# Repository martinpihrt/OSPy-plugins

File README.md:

# OSPy-plugins

### A collection of user contributed plugins for the Raspberry Pi based irrigation controll software OSPy - Open Sprinkler Python (OSPy).

Please note: Unless otherwise stated: This is free software: you can redistribute it and/or modify it under the terms of the GNU General Public License as published by the Free Software Foundation, either version 3 of the License, or (at your option) any later version.

## Documentation

The complete [OSPy-plugins Wiki](https://github.com/martinpihrt/OSPy-plugins/wiki) explains what every official plug-in is for, how it works, how to install and configure it, its dependencies, hardware, permissions and troubleshooting steps. Start with [Getting started](https://github.com/martinpihrt/OSPy-plugins/wiki/Getting-Started) or browse the [plug-in catalog](https://github.com/martinpihrt/OSPy-plugins/wiki/Plugin-Catalog).

## Stable and test channels

The `master` branch is the stable channel selected by OSPy by default. New plug-in changes are developed and verified in the `beta` branch first. After successful practical and automated testing, the same commits can be promoted from `beta` to `master` without rebuilding or changing them.

GitHub Actions runs the OSPy test suite on every push and pull request to `beta` or `master`. The tested plug-in revision is checked against both the OSPy `master` and OSPy `beta` branches on Python 3.11 and Python 3.14. All four jobs must pass before a beta change is promoted to the stable channel. Python 3.11 remains the Raspberry Pi OS Bookworm baseline and Python 3.14 verifies compatibility with the latest stable Python feature release.

## Declared permission approval

Every `plugin.json` must declare only the permissions the plug-in actually uses: `network`, `files`, `i2c`, `gpio`, `email`, `subprocess` and/or `system`. Starting with OSPy 3.0.294, newly installed plug-ins require explicit administrator approval of that complete set before their Python code starts. An update with the same or fewer permissions keeps its approval. Adding a permission requires a new approval and is skipped by automatic update until it has been reviewed. Existing installed plug-ins are approved once during the backward-compatible OSPy upgrade migration, including disabled plug-ins.

This is administrative consent and an audit record, not operating-system sandboxing. Plug-in authors must increase the manifest version whenever code or declared requirements change and must never omit a permission merely to avoid the approval prompt.

These programs are distributed in the hope that they will be useful, but WITHOUT ANY WARRANTY; without even the implied warranty of MERCHANTABILITY or FITNESS FOR A PARTICULAR PURPOSE. See the GNU General Public License for more details. http://opensource.org/licenses/gpl-3.0.html

Theses I2C addresses is used in available plugins:
* air_temp_humi	0x03<br>
* tank_monitor 	0x04<br>
* button_contr	0x27<br>
* lcd_display 	0x20-0x27, 0x38-0x3F<br>
* real_time 	0x68<br>
* volt_temp_da 	0x48<br>
* water_meter 	one selectable address: 0x50 or 0x51<br>
* wind_monitor 	one selectable address: 0x50 or 0x51<br>
* current_loop_tanks_monitor 0x48, 0x49, 0x4A, 0x4B<br>

Address conflicts, selectable alternatives and wiring requirements are documented in [Hardware and I²C](https://github.com/martinpihrt/OSPy-plugins/wiki/Hardware-and-I2C) and on the individual plug-in pages.

## Available plug-ins

This table is generated from the `name`, `version` and `description` fields in every official `plugin.json`. Run `python tools/generate_plugin_table.py` after changing a manifest and `python tools/generate_plugin_table.py --check` to verify that the README is current.

<!-- plugin-table:start -->
| Plug-in | Version | Description |
| --- | --- | --- |
| [**Air Temperature and Humidity Monitor**](https://github.com/martinpihrt/OSPy-plugins/wiki/Plugin-air-temp-humi) | `1.0.7` | Monitors DHT temperature and humidity and optional DS18B20 sensors through an external I2C board. |
| [**Astro Sunrise and Sunset**](https://github.com/martinpihrt/OSPy-plugins/wiki/Plugin-sunrise-and-sunset) | `1.0.6` | Calculates astronomical dawn, sunrise, noon, sunset and dusk times for OSPy programs and mobile clients. |
| [**Automation Rules**](https://github.com/martinpihrt/OSPy-plugins/wiki/Plugin-automation-rules) | `1.1.4` | Builds graphical AND/OR rules over cached provider and OSPy values, sends detailed notifications and optionally performs guarded control actions with incident locking. |
| [**Button Control**](https://github.com/martinpihrt/OSPy-plugins/wiki/Plugin-button-control) | `1.0.0` | Controls OSPy functions through eight MCP23017 I2C buttons and indicator LEDs. |
| [**CHMI**](https://github.com/martinpihrt/OSPy-plugins/wiki/Plugin-chmi) | `1.0.7` | Downloads CHMI or SHMU radar data, detects local rain and optionally controls a hardware map. |
| [**CLI Control**](https://github.com/martinpihrt/OSPy-plugins/wiki/Plugin-cli-control) | `1.0.0` | Runs administrator-configured shell commands when OSPy station states change. |
| [**Current Loop Tanks Monitor**](https://github.com/martinpihrt/OSPy-plugins/wiki/Plugin-current-loop-tanks-monitor) | `1.1.1` | Monitors up to four water tanks through an ADS1115 and 4-20 mA pressure sensors. |
| [**Database Connector**](https://github.com/martinpihrt/OSPy-plugins/wiki/Plugin-database-connector) | `1.1.3` | Provides shared MySQL access, backup and durable queued writes for OSPy plug-ins. |
| [**Direct 16 Relay Outputs**](https://github.com/martinpihrt/OSPy-plugins/wiki/Plugin-relay-16) | `1.0.0` | Controls up to 16 direct Raspberry Pi GPIO relay outputs with configurable trigger polarity. |
| [**Door Opening**](https://github.com/martinpihrt/OSPy-plugins/wiki/Plugin-door-opening) | `1.0.0` | Activates a selected OSPy station for a bounded door or gate opening interval. |
| [**E-mail Notifications**](https://github.com/martinpihrt/OSPy-plugins/wiki/Plugin-email-notifications) | `1.0.1` | Sends OSPy event notifications through a STARTTLS SMTP server with an optional retry queue. |
| [**E-mail Notifications SSL**](https://github.com/martinpihrt/OSPy-plugins/wiki/Plugin-email-notifications-ssl) | `1.1.6` | Sends OSPy event and login notifications through SMTP over SSL with an optional retry queue. |
| [**E-mail Reader**](https://github.com/martinpihrt/OSPy-plugins/wiki/Plugin-email-reader) | `1.0.0` | Reads authenticated IMAP commands and controls OSPy programs, stations and system functions. |
| [**Energy Meter**](https://github.com/martinpihrt/OSPy-plugins/wiki/Plugin-energy-meter) | `1.0.7` | Monitors Shelly three-phase electricity meters and stores import, export, tariff, cost and solar calculations. |
| [**Home Assistant**](https://github.com/martinpihrt/OSPy-plugins/wiki/Plugin-mqtt-home-assistant) | `1.0.1` | Publishes OSPy devices, controls and sensor values through Home Assistant MQTT Discovery. |
| [**IP Cam**](https://github.com/martinpihrt/OSPy-plugins/wiki/Plugin-ip-cam) | `1.0.0` | Downloads, caches and proxies JPEG, GIF and MJPEG images from IP cameras. |
| [**IP Scanner**](https://github.com/martinpihrt/OSPy-plugins/wiki/Plugin-ip-scanner) | `1.0.0` | Scans the local network for devices, names, MAC addresses and common web services. |
| [**Irrigation Safety**](https://github.com/martinpihrt/OSPy-plugins/wiki/Plugin-irrigation-safety) | `1.0.0` | Monitors irrigation flow, pressure and tank level, learns station flow ranges and can stop outputs and disable the scheduler when a confirmed fault occurs. |
| [**Label Maker**](https://github.com/martinpihrt/OSPy-plugins/wiki/Plugin-labelmaker) | `1.0.0` | Generates EAN13 barcodes and configurable QR code images. |
| [**LCD Display**](https://github.com/martinpihrt/OSPy-plugins/wiki/Plugin-lcd-display) | `1.0.2` | Displays OSPy status information on a 16x2 HD44780 LCD through a PCF8574 I2C expander. |
| [**Modbus Stations**](https://github.com/martinpihrt/OSPy-plugins/wiki/Plugin-modbus-stations) | `1.0.0` | Controls OSPy station outputs through Modbus RTU serial relay boards. |
| [**Monthly Water Level**](https://github.com/martinpihrt/OSPy-plugins/wiki/Plugin-monthly-water-level) | `1.0.1` | Applies a configurable irrigation percentage adjustment for each calendar month. |
| [**MQTT**](https://github.com/martinpihrt/OSPy-plugins/wiki/Plugin-mqtt) | `1.0.1` | Shared MQTT client, status publishing and remote OSPy control. |
| [**Network Ping Monitor**](https://github.com/martinpihrt/OSPy-plugins/wiki/Plugin-network-ping-monitor) | `1.0.2` | Monitors three network targets through ICMP and optionally logs availability and latency. |
| [**OSPy package Backup**](https://github.com/martinpihrt/OSPy-plugins/wiki/Plugin-ospy-backup) | `1.0.5` | Creates downloadable ZIP archives of installed plug-in data directories. |
| [**Photovoltaic Boiler**](https://github.com/martinpihrt/OSPy-plugins/wiki/Plugin-photovoltaic-boiler) | `1.0.0` | Controls boiler heating between photovoltaic surplus and the public grid using configured temperature sources. |
| [**Ping Monitor**](https://github.com/martinpihrt/OSPy-plugins/wiki/Plugin-ping-monitor) | `1.0.0` | Monitors host reachability, logs outages and can notify or restart a device after repeated failures. |
| [**Pool Heating**](https://github.com/martinpihrt/OSPy-plugins/wiki/Plugin-pool-heating) | `1.0.0` | Controls a pool circulation pump from pool and solar collector temperatures. |
| [**Pressure Monitor**](https://github.com/martinpihrt/OSPy-plugins/wiki/Plugin-pressure-monitor) | `1.1.1` | Checks binary pipe pressure while the master station runs and can stop irrigation when pressure is missing. |
| [**Pressurizer**](https://github.com/martinpihrt/OSPy-plugins/wiki/Plugin-pressurizer) | `1.0.0` | Pre-runs the master pump to build pressure before selected irrigation stations start. |
| [**Proto**](https://github.com/martinpihrt/OSPy-plugins/wiki/Plugin-proto) | `1.0.0` | Provides a minimal working example and starting point for developing OSPy plug-ins. |
| [**Pulse Output Test**](https://github.com/martinpihrt/OSPy-plugins/wiki/Plugin-pulse) | `1.0.0` | Pulses a selected OSPy station at 1 Hz for a bounded valve-location test. |
| [**Real Time and NTP time**](https://github.com/martinpihrt/OSPy-plugins/wiki/Plugin-real-time) | `1.0.1` | Synchronizes system time with NTP and supported I2C real-time clocks. |
| [**Relay Test**](https://github.com/martinpihrt/OSPy-plugins/wiki/Plugin-relay) | `1.0.0` | Runs a bounded test of the OSPy relay output. |
| [**Remote FTP Control**](https://github.com/martinpihrt/OSPy-plugins/wiki/Plugin-remote-ftp-control) | `1.0.0` | Exchanges command and status files through FTP for legacy remote control of OSPy. |
| [**Remote Notifications**](https://github.com/martinpihrt/OSPy-plugins/wiki/Plugin-remote-notifications) | `1.0.0` | Sends OSPy status and event notifications to a configured remote PHP and SQL web service. |
| [**RS485 Communication**](https://github.com/martinpihrt/OSPy-plugins/wiki/Plugin-rs485-communication) | `1.0.3` | Provides a central RS485 worker and FIFO rs485_queue for OSPy plug-ins, with Waveshare CH343G auto-detection, status monitoring and adapter testing. |
| [**Shelly Cloud Integration**](https://github.com/martinpihrt/OSPy-plugins/wiki/Plugin-shelly-cloud-integrator) | `1.0.8` | Loads and caches configured Shelly device states from the Shelly Cloud API for OSPy and other plug-ins. |
| [**Signaling Examples**](https://github.com/martinpihrt/OSPy-plugins/wiki/Plugin-signaling-examples) | `1.0.0` | Demonstrates OSPy and plug-in signal subscriptions and records received events. |
| [**SMS Modem**](https://github.com/martinpihrt/OSPy-plugins/wiki/Plugin-sms-adj) | `1.0.0` | Receives authorized SMS commands through a Gammu-compatible modem and returns OSPy status by SMS. |
| [**Speed Monitor**](https://github.com/martinpihrt/OSPy-plugins/wiki/Plugin-speed-monitor) | `1.0.0` | Measures and logs Internet ping, download and upload performance at scheduled intervals. |
| [**System Debug Information**](https://github.com/martinpihrt/OSPy-plugins/wiki/Plugin-system-debug) | `1.0.1` | Displays, downloads and clears the OSPy technical debug log. |
| [**System Information**](https://github.com/martinpihrt/OSPy-plugins/wiki/Plugin-system-info) | `1.0.1` | Displays operating-system, hardware, network, process, storage, USB, serial and optional I2C information. |
| [**System Update**](https://github.com/martinpihrt/OSPy-plugins/wiki/Plugin-system-update) | `1.2.8` | Checks, installs and safely rolls back OSPy updates from stable or beta Git branches with backup and watchdog protection. |
| [**System Watchdog**](https://github.com/martinpihrt/OSPy-plugins/wiki/Plugin-system-watchdog) | `1.0.0` | Configures and monitors the Raspberry Pi hardware watchdog to recover from system lockups. |
| [**Telegram Bot**](https://github.com/martinpihrt/OSPy-plugins/wiki/Plugin-telegram-bot) | `1.0.1` | Sends Telegram notifications and accepts a limited set of OSPy control commands from subscribed chats. |
| [**Temperature Switch**](https://github.com/martinpihrt/OSPy-plugins/wiki/Plugin-temperature-switch) | `1.0.0` | Starts and stops OSPy programs from configured temperature sources and hysteresis limits. |
| [**Thermostat**](https://github.com/martinpihrt/OSPy-plugins/wiki/Plugin-thermostat) | `1.1.4` | Controls up to 20 OSPy programs from temperature sources, hysteresis limits, operating windows and a heating-water condition. |
| [**UPS Monitor**](https://github.com/martinpihrt/OSPy-plugins/wiki/Plugin-ups-adj) | `1.0.5` | Monitors mains power and can notify, shut down OSPy and switch off a UPS after a sustained outage. |
| [**Usage Statistics**](https://github.com/martinpihrt/OSPy-plugins/wiki/Plugin-usage-statistics) | `1.0.1` | Downloads and displays anonymized public OSPy usage statistics. |
| [**Venetian Blind**](https://github.com/martinpihrt/OSPy-plugins/wiki/Plugin-venetian-blind) | `1.2.8` | Controls configured Shelly or compatible blinds, including tilt positions, automation rules and mobile actions. |
| [**Voice Notification**](https://github.com/martinpihrt/OSPy-plugins/wiki/Plugin-voice-notification) | `1.0.0` | Plays scheduled voice announcements before configured OSPy program and station events. |
| [**Voice Station**](https://github.com/martinpihrt/OSPy-plugins/wiki/Plugin-voice-station) | `1.0.0` | Queues and plays audio when station outputs change, regardless of what triggered the station. |
| [**Voltage and Temperature Monitor**](https://github.com/martinpihrt/OSPy-plugins/wiki/Plugin-volt-temp-da) | `1.0.0` | Measures and logs voltages or LM35 temperatures through a PCF8591 I2C converter. |
| [**Water Consumption Counter**](https://github.com/martinpihrt/OSPy-plugins/wiki/Plugin-water-consumption-counter) | `1.2.7` | Estimates and reports water consumption from configured station flow rates and master-station runtime. |
| [**Water Meter**](https://github.com/martinpihrt/OSPy-plugins/wiki/Plugin-water-meter) | `1.2.1` | Measures pulse-output water meters through a PCF8583 counter with live flow, history, CSV and optional SQL logging. |
| [**Water Tank Monitor**](https://github.com/martinpihrt/OSPy-plugins/wiki/Plugin-tank-monitor) | `1.1.1` | Measures ultrasonic tank level and volume, blocks irrigation on low water and exposes tank provider actions. |
| [**Weather Dashboard**](https://github.com/martinpihrt/OSPy-plugins/wiki/Plugin-weather-dashboard) | `1.0.2` | Displays selected OSPy sensor and plug-in values as configurable gauges or text. |
| [**Weather Stations**](https://github.com/martinpihrt/OSPy-plugins/wiki/Plugin-weather-stations) | `1.0.0` | Displays selected OSPy sensor and plug-in values as configurable gauges or text. |
| [**Weather-based Rain Delay**](https://github.com/martinpihrt/OSPy-plugins/wiki/Plugin-weather-based-rain-delay) | `1.0.0` | Sets OSPy rain delay from measured or Netatmo rainfall and configured weather thresholds. |
| [**Weather-based Water Level**](https://github.com/martinpihrt/OSPy-plugins/wiki/Plugin-weather-based-water-level) | `1.1.2` | Calculates hourly OSPy water-level adjustment from weather balance, Zimmerman or evapotranspiration methods. |
| [**Weather-based Water Level Netatmo**](https://github.com/martinpihrt/OSPy-plugins/wiki/Plugin-weather-based-water-level-netatmo) | `1.0.0` | Adjusts OSPy water level using rainfall history from a configured Netatmo rain module. |
| [**Webcam Monitor**](https://github.com/martinpihrt/OSPy-plugins/wiki/Plugin-webcam) | `1.0.0` | Captures and serves snapshots from a Linux USB webcam using fswebcam. |
| [**Wind Speed Monitor**](https://github.com/martinpihrt/OSPy-plugins/wiki/Plugin-wind-monitor) | `1.2.3` | Measures wind through PCF8583 or Modbus sensors and can log, notify or run safety actions. |
<!-- plugin-table:end -->

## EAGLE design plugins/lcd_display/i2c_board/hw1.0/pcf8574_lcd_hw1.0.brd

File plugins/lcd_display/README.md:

LCD Settings Readme
====

Version 1.0.1 disconnects all OSPy signal receivers when the plug-in worker
stops, preventing stale callbacks after a plug-in restart.

Tested in Python 3+

This plugin shows information on 16x2 character LCD with PCF8574.  
Automatically detects the display at the following I2C addresses: 0x20-0x27, 0x38-0x3F.  
Compatible with the HD44780 controller.  

The plug-in includes an OSPy `plugin.json` manifest, uses the shared plug-in runtime and implements `health()`. Diagnostics reports whether the display function and worker are running, the detected I2C address, the last successful LCD update and the most recent I2C error. A temporarily busy shared I2C bus is reported as a warning; a persistent write error is reported as an error.

Plugin setup
-----------
* Check Use I2C LCD:  
  If checked use I2C lcd plugin is enabled and print messages on the LCD display.  </br>

* HW version I2C PCF8574<->LCD:  
  Select type Hardware board with PCF8574. Conection with LCD driver:  
  a) Lower 4 bits of expander are commands bits  
  b) Top 4 bits of expander are commands bits AND P0-4 P1-5 P2-6 (Use for LCD1602 board)  
  c) Top 4 bits of expander are commands bits AND P0-6 P1-5 P2-4  
  d) LCD1602 board where lower 4 are commands, but backlight is pin 3  
  e) LCD board (https://pihrt.com/clanky/arduino-uno-deska-i2c-lcd-16x2)  </br>

* Check Use print lines to debug files:  
  If checked use print lines to debug files line 1 or line 2 print to debug files.  
  (warning: If you enable this debug file will have a huge size).  </br>

* Display: If checked print state message to LCD display
System Name:  
SW Version Date:  
IP:  
Port:  
CPU Temp:  
Time and Date:
Uptime:  
Rain Sensor:  
Last Run Program:  
Pressure Sensor:  
Water Tank Level:  
Running Stations:  
DS18B20 Temperature: </br>
Wind Speed:
Shows current wind speed and maximum wind speed from the Wind Speed Monitor plugin in the format `actual (max) unit`. </br>

The LCD controller is re-initialized at the start of each display cycle without re-scanning the I2C address. This helps recover HD44780/PCF8574 displays that drift into corrupted characters during long running operation. </br>

* Status:
  Status window from the plugin.  
  Example message on the LCD display:  
  OpenSprinkler Py (text on line 1)
  Irrigation system (text on line 2)    
  CPU temperature:  
  42.8 C  
  Date: 17.02.2015  
  Time: 12:22:57  
  OSPy version:  
  2015-02-17  
  System uptime:  
  5:12:11  
  My IP is:  
  https://192.168.4.184/8080  
  My port is:  
  8080  
  Rain sensor:  
  Inactive  
  Last program:  
  None  
  Pressure sensor:    
  Not available  
  Water Tank Level:
  Level 120 cm 100%, volume 1.25 m3, ping 86 cm
  DS1-6 Temperature:  
  23.5, -127, 23.5, 36.5, 78.0, -127
  (-127 is not connected probe to hardware board...)  </br>

* Important status information OSPy:
  If events occur in the system: restart, poweroff, update available, they will be displayed preferentially regardless of the above settings.  </br>     
  
## The hardware should be connected as follows (LCD board by pihrt.com)

## The LCD 1602 IIC with PCF8574 (Top 4 bits of expander are commands bits AND P0-4 P1-5 P2-6)

## PCF8574 address map

Visit [Martin Pihrt's blog](https://pihrt.com/clanky/arduino-uno-deska-i2c-lcd-16x2). for more information.

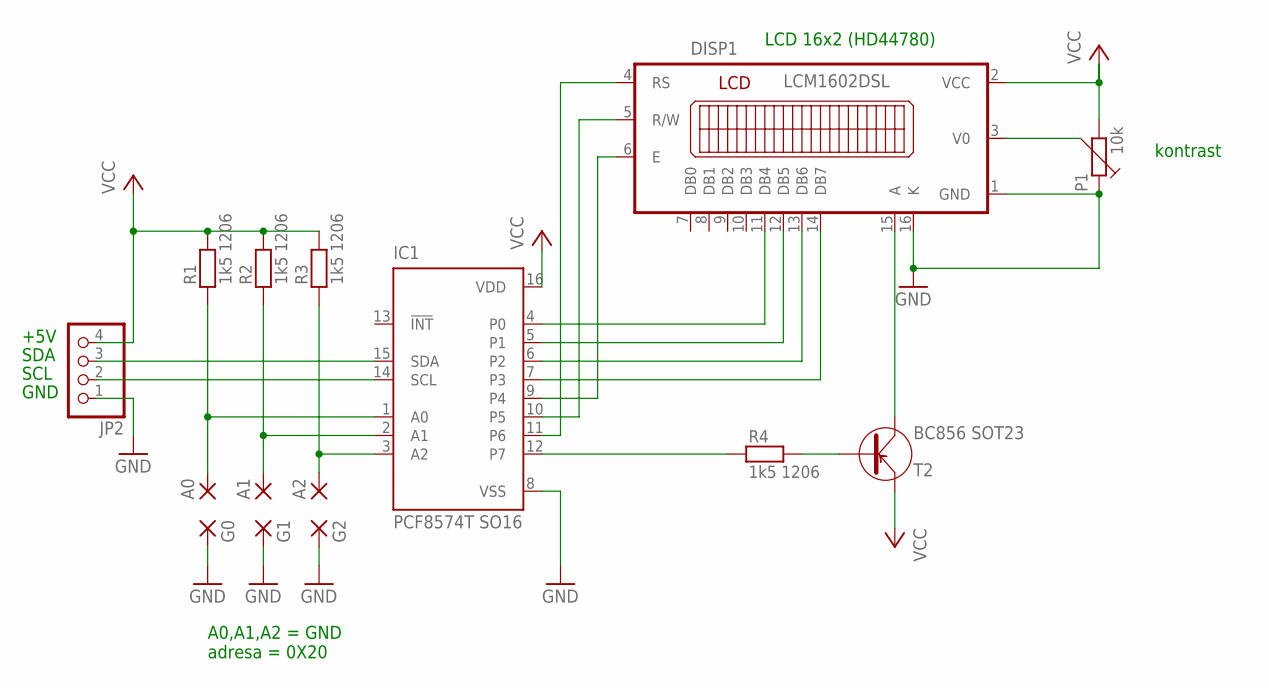
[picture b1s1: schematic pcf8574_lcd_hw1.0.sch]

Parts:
A0, A1, A2: SMD2; SMD1,27-2,54
DISP1: LCM1602DSL
G0, G1, G2: SMD2; SMD1,27-2,54
IC1: PCF8574T SO16; SO16W
JP2: PINHD-1X4; 1X04
P1: 10k; PT10V
R1, R2, R3, R4: 1k5 1206; 1206
T2: BC856 SOT23; SOT-23

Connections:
GND: DISP1.1 (GND), DISP1.16 (K), G0.1, G1.1, G2.1, IC1.8 (VSS), JP2.1, P1.1
unnamed: IC1.15 (SDA), JP2.3
unnamed: IC1.14 (SCL), JP2.2
unnamed: DISP1.3 (V0), P1.3
unnamed: DISP1.15 (A), T2.3 (C)
unnamed: DISP1.4 (RS), IC1.11 (P6)
unnamed: DISP1.5 (R/W), IC1.10 (P5)
unnamed: DISP1.6 (E), IC1.9 (P4)
unnamed: DISP1.14 (DB7), IC1.7 (P3)
unnamed: IC1.12 (P7), R4.1
unnamed: A0.1, IC1.1 (A0), R1.1
unnamed: A2.1, IC1.3 (A2), R3.1
unnamed: A1.1, IC1.2 (A1), R2.1
unnamed: DISP1.13 (DB6), IC1.6 (P2)
unnamed: DISP1.12 (DB5), IC1.5 (P1)
unnamed: DISP1.11 (DB4), IC1.4 (P0)
unnamed: R4.2, T2.1 (B)
VCC: DISP1.2 (VCC), IC1.16 (VDD), JP2.4, P1.2, R1.2, R2.2, R3.2, T2.2 (E)

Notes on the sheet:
+5V
SDA
SCL
GND
kontrast
A0,A1,A2 = GND adresa = 0X20
LCD 16x2 (HD44780)

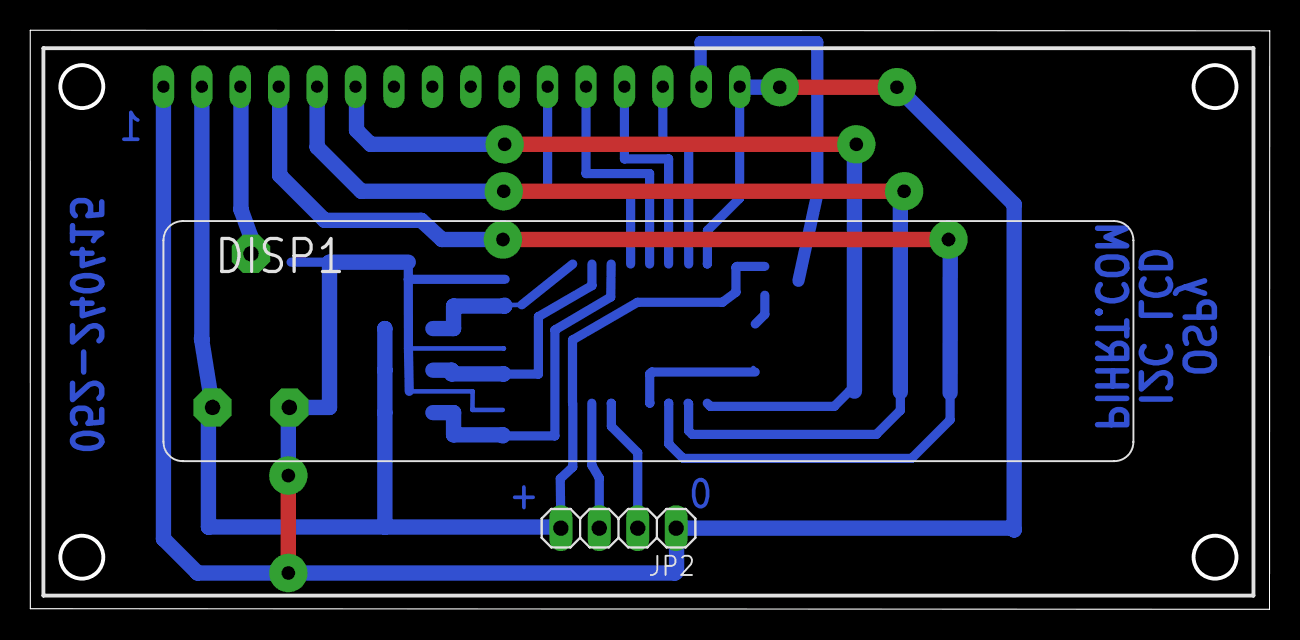
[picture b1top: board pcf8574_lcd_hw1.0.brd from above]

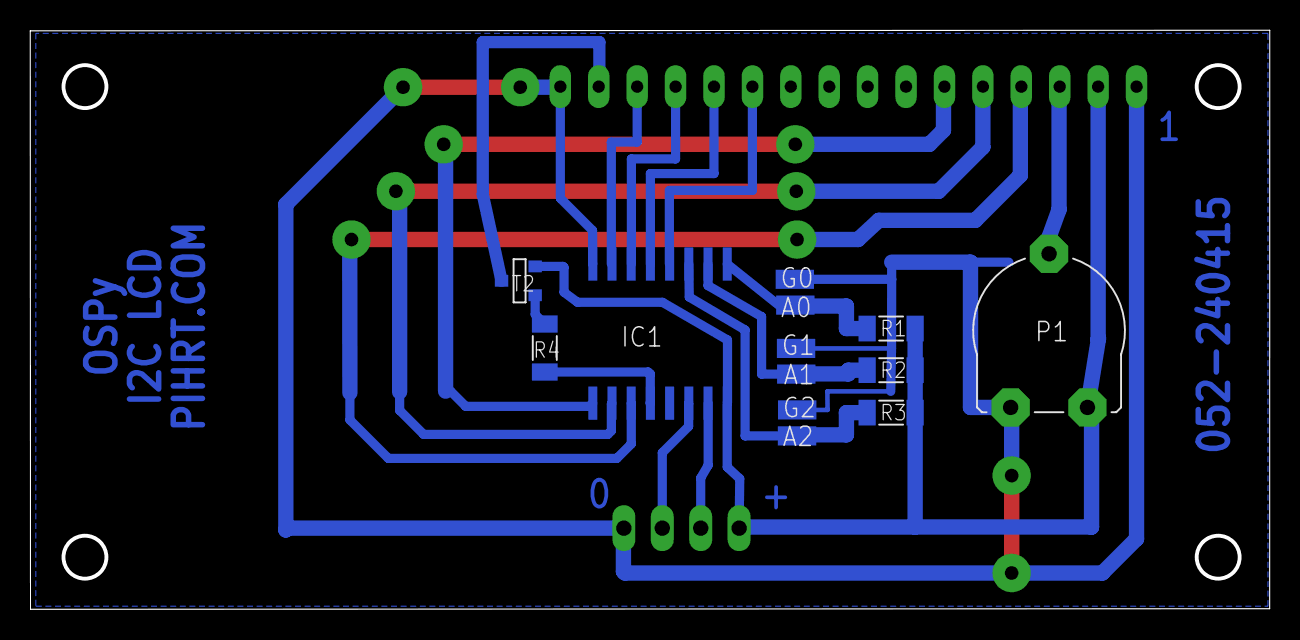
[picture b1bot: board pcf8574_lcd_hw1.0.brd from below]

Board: 2 copper layers, 82.0 x 38.3 mm, 15 parts (13 on the bottom side), 18 nets.

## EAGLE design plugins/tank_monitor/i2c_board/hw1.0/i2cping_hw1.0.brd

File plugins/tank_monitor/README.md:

Tank Monitor Readme
====

Tested in Python 3+

The plug-in includes a `plugin.json` manifest and reports its worker, configured
I²C address, water level, fill, sensor distance, volume, regulation, watering
block, latest reading and errors through the OSPy system health interface.

Version 1.1.1 adds explicit Automation Rules provider actions for safely stopping the active tank-regulation output and resetting the recorded minimum and maximum to the latest available level. Version 1.1.0 implements the read-only `ospy.provider.v1` contract for the single ultrasonic tank. Cached level, fill, distance and volume are available in stable units without triggering an I²C measurement.

This plugin measures the water level in the tank. If water level is small, this plugin stop irigation system (stop runing stations in scheduler) and sends E-mail with error Safety for master station pump if no water.

Plugin setup
-----------
* Check Use ultrasonic measuring the water level in the tank:    
  If checked measures the water level in the tank is active.  

* The distance from the sensor to the minimum water level in the tank:  
  Enter the distance from the sensor to the minimum water level in the tank (the tank bottom).  

* The distance from the sensor to the maximum water level in the tank:  
  Enter the distance from the sensor to the maximu water level in the tank (maximum to sensor - 2cm).  

* The water level from the bottom to the minimum water level in the tank:  
  Enter the level for the minimum water level in the tank.   

* Stop stations if minimum water level:  
  Stoping these stations if is minimum water level in the tank. Selector for stop stations in scheduler.

* Stop stations if sonic probe has fault:  
  If the level sensor fails, the above selected stations in the scheduler will stop.

* Cylinder diameter for volume calculation:  
  Enter the diameter for volume calculation.

* Display as liters or m3:  
  Show measured water as liters or m3.

* Use averaging for samples:
  If checked, averaging of measured values will be performed (this option affects the speed of response to the measured value

* Number of samples for average:  
  Enter the number count for samples
  
* Send an E-mail with an error that there is minimum water in the tank:  
  For this function required E-mail plugin.

* Send an E-mail with an error if sonic probe has fault:   
  For this function required E-mail plugin.

* Regulate the maximum water level:  
  If checked, regulation have the maximal water level active.

* Maximum maintained water level:  
  If the measured water level exceeds this set value, the output is activated.  

* Maximum run time in activate:  
  Maximum duration when activating the output (in minutes and seconds). After this time, the output will turn off regardless of other events (conditions).    

* Minimum maintained water level:  
  If the measured water level falls below this set value, the output is deactivated.   

* Select Output for regulation:  
  Select Output for regulation zones.

* Enable local logging:  
  Enable logging and graphing.

* Check Enable SQL logging:  
  If checked enabled logging save measure value to SQL database. This option requires the Database Connector extension to be installed and configured. The button will delete the tankmonitor table from the database, thus deleting all saved data from this extension! This promotion is non-refundable!  

* Maximum number of log records:  
  Maximum number of log records (only for csv file).

* Interval for logging:  
  Logging interval (minimum 1 minute).

* Enable bus logging:
  Logging for advanced user (save debug data from I2C bus).

* Only if data changed:
  Logging of data only when this data changes, otherwise still logging.    

* Select filter for graph history  
  From - To selector (date time)

* Status:  
  Status window from the plugin.  

The hardware should be connected as follows:  

Visit [Martin Pihrt's blog](https://pihrt.com/clanky/moje-raspberry-pi-plugin-ospy-vlhkost-pudy-a-mozstvi-vody-v-tankua). for more information.

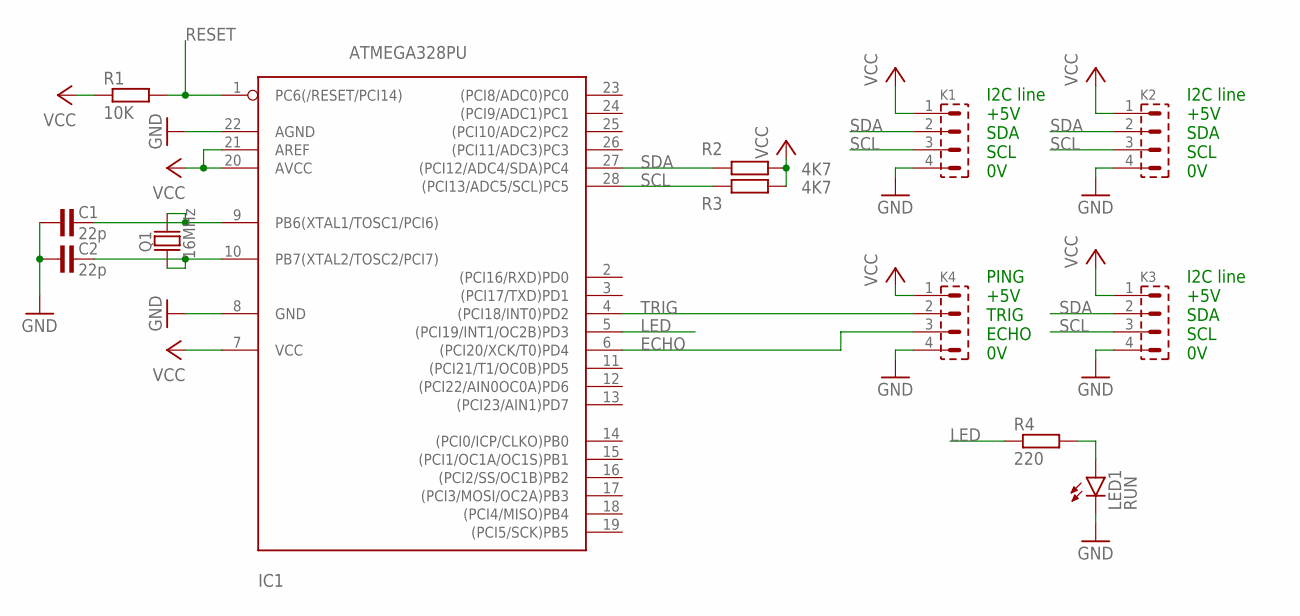
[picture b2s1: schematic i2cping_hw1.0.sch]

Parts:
C1, C2: 22p; C-5
IC1: ATMEGA328PU; DIL28-3
K1, K2, K3, K4: PSH02-04P
LED1: RUN; LED5MM
Q1: 16MHz; HC-49U
R1: 10K; 0207/7
R2, R3: 4K7; 0207/7
R4: 220; 0207/7

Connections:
ECHO: IC1.6 ((PCI20/XCK/T0)PD4), K4.3
GND: C1.1, C2.1, IC1.8 (GND), IC1.22 (AGND), K1.4, K2.4, K3.4, K4.4, LED1.K (C)
LED: IC1.5 ((PCI19/INT1/OC2B)PD3), R4.1
unnamed: C1.2, IC1.9 (PB6(XTAL1/TOSC1/PCI6)), Q1.2
unnamed: LED1.A, R4.2
Q1: C2.2, IC1.10 (PB7(XTAL2/TOSC2/PCI7)), Q1.1
RESET: IC1.1 (PC6(/RESET/PCI14)), R1.2
SCL: IC1.28 ((PCI13/ADC5/SCL)PC5), K1.3, K2.3, K3.3, R3.2
SDA: IC1.27 ((PCI12/ADC4/SDA)PC4), K1.2, K2.2, K3.2, R2.2
TRIG: IC1.4 ((PCI18/INT0)PD2), K4.2
VCC: IC1.7 (VCC), IC1.20 (AVCC), IC1.21 (AREF), K1.1, K2.1, K3.1, K4.1, R1.1, R2.1, R3.1

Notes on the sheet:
I2C line +5V SDA SCL 0V
PING +5V TRIG ECHO 0V

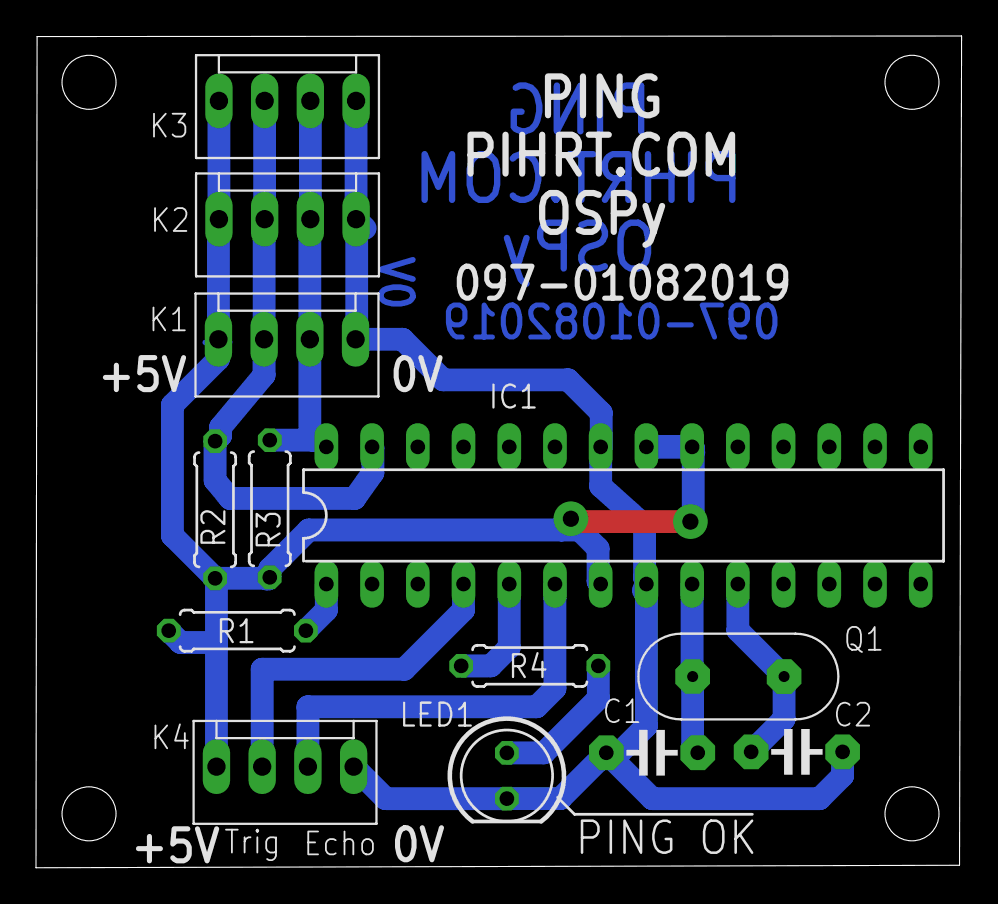
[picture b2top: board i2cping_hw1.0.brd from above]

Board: 2 copper layers, 51.4 x 46.2 mm, 13 parts (0 on the bottom side), 11 nets.

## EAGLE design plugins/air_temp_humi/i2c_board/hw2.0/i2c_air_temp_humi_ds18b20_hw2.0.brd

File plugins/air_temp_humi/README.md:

Air Temperature and Humidity Monitor Readme
====

Tested in Python 3+

Version 1.0.3 treats Database Connector as an optional runtime dependency.
When it is stopped, sensor sampling and local logging continue and SQL logging
is skipped without repeated error tracebacks.

This plugin needs DHT11 (22) probe connected to GPIO 10 (pin 19 MOSI).   
This plugin allows you to connect 1-6 DS18B20 sensors connected to the external hardware board via an I2C bus (address 0x03). 
Visit [Martin Pihrt's blog](https://pihrt.com/clanky/moje-raspberry-pi-plugin-ospy-mereni-teploty-pomoci-ds18b20). for more information for HW.

The plug-in includes an OSPy `plugin.json` manifest, registers its sensor worker
with the shared plug-in runtime, uses the common stop signal, and implements
`health()`. Diagnostics evaluates only the configured DHT and DS18B20 sensor
types and reports worker state, enabled probes, latest successful sample, and
the latest sensor error.

Plugin setup
-----------

* Check Enabled:  
  If checked enabled plugin is enabled.

* Check Enable local logging and show graph:  
  If checked enabled logging save measure value to logfile (format .csv for Excel) and logfile for graph.

* Check Enable SQL logging:  
  If checked enabled logging save measure value to SQL database. This option requires the Database Connector extension to be installed and configured. The button will delete the airtemp table from the database, thus deleting all saved data from this extension! This promotion is non-refundable!

* Maximum number of log records:  
  Type maximum records in log file. 0 is unlimited.  

* Interval for logging:  
  Type interval for logging in minutes (minimum is 1).

* Label for sensor:  
  Type label for Your probe.

* Check Allow regulation:  
  If checked "Allow regulation", now is output regulation enabled.

* Hysteresis:  
  Number value for hysteresis in regulation loop.

* Humidity for output ON:  
  Humidity value for output switched to on.

* Maximum run time in activate:  
  Maximum duration when activating the output (in minutes and seconds). After this time, the output will turn off regardless of other events (conditions).  

* Humidity for output OFF:  
  Humidity value for output switched to off.

* Select Output:  
  Select station for output.

* Check Enable DS18B20:  
  If checked enabled DS18B20, I2C bus is in plugin enabled.

* DS18B20 error timeout:  
  Time in seconds for keeping the last valid DS18B20 value when an I2C read returns an error value such as -127. During this time the plugin does not overwrite the displayed/logged value with the error value. Use 0 to keep the last valid value without timeout.

* DS18B20 sensors:  
  Enable only the connected DS18B20 sensors (DS1-DS6) and set a label for each used sensor. Disabled sensors are hidden from the graph and log view.
  
* Label for sensor DS 1-6:  
  Type label for Your probe Dallas DS18B20.

* Status:  
  Status window from the plugin.

* Graph
  To use the graph it is necessary to enable saving of measured data (from temperature sensors). When using for the first time, name the sensors first and then delete all records (using the button). 

* Select filter for graph history  
  Without limits  
  Day filter  
  Month filter  
  Year filter

Visit [Martin Pihrt's blog](https://pihrt.com/clanky/moje-raspberry-pi-plugin-ospy-mereni-teploty-pomoci-ds18b20). for more information HW board with DS18B20 probe.

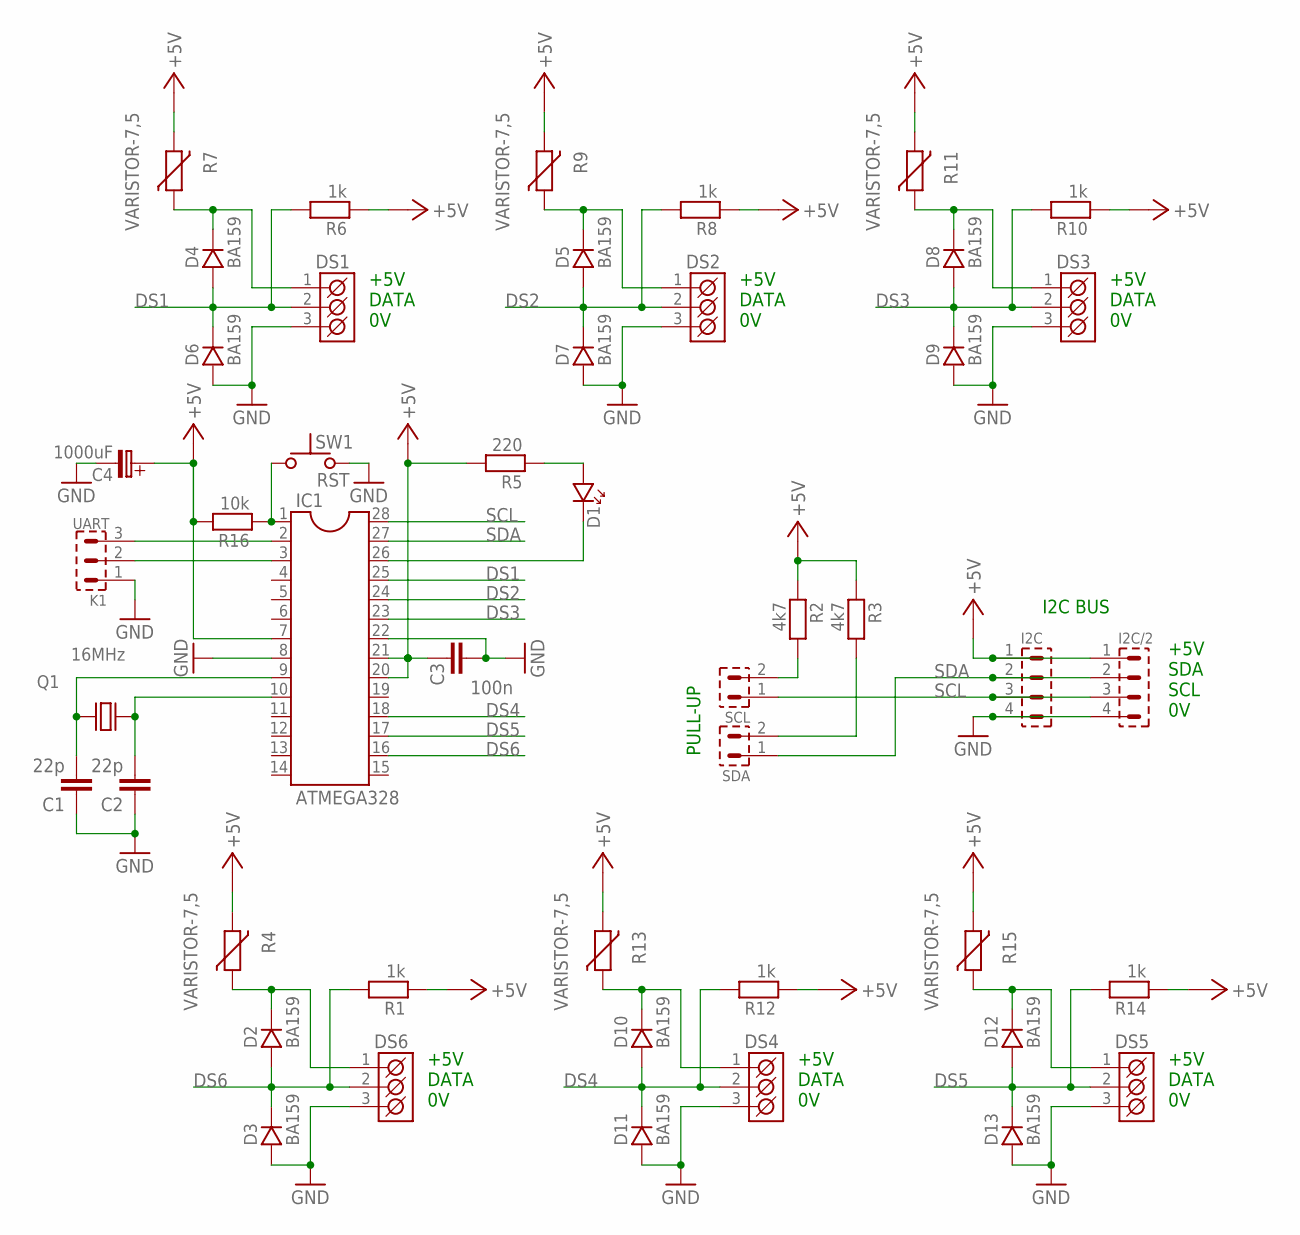
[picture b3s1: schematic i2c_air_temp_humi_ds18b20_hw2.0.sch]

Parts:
C1, C2: 22p; C5B3
C3: 100n; C5B3
C4: 1000uF; C-EL_5
D1: LED_3
D2, D3, D4, D5, D6, D7, D8, D9, D10, D11, D12, D13: BA159; DO41
DS1, DS2, DS3, DS4, DS5, DS6: ARK500/3
I2C, I2C/2: PSH02-04P
IC1: ATMEGA328; DIL28-3
K1: UART; PSH02-03P
Q1: 16MHz; HC-49U
R1, R6, R8, R10, R12, R14: 1k; R-7,5
R2, R3: 4k7; R-7,5
R4, R7, R9, R11, R13, R15: VARISTOR-7,5; R-7,5
R5: 220; R-7,5
R16: 10k; R-7,5
SCL: S1G2_JUMP; S1G2_JUM
SDA: S1G2_JUMP; S1G2_JUM
SW1: RST; P-B1720

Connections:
+5V: C3.1, C4.C+ (C_EL+), I2C.1, I2C/2.1, IC1.7, IC1.20, IC1.21, R1.1, R2.1, R3.1, R4.2, R5.2, R6.1, R7.2, R8.1, R9.2, R10.1, R11.2, R12.1, R13.2, R14.1, R15.2, R16.2
DS1: D4.A, D6.K, DS1.2 (K2), IC1.25, R6.2
DS2: D5.A, D7.K, DS2.2 (K2), IC1.24, R8.2
DS3: D8.A, D9.K, DS3.2 (K2), IC1.23, R10.2
DS4: D10.A, D11.K, DS4.2 (K2), IC1.18, R12.2
DS5: D12.A, D13.K, DS5.2 (K2), IC1.17, R14.2
DS6: D2.A, D3.K, DS6.2 (K2), IC1.16, R1.2
GND: C1.1, C2.1, C3.2, C4.C- (C_EL-), D3.A, D6.A, D7.A, D9.A, D11.A, D13.A, DS1.3 (K3), DS2.3 (K3), DS3.3 (K3), DS4.3 (K3), DS5.3 (K3), DS6.3 (K3), I2C.4, I2C/2.4, IC1.8, IC1.22, K1.1, SW1.2
unnamed: D2.K, DS6.1 (K1), R4.1
unnamed: C2.2, IC1.10, Q1.1
unnamed: D1.K, IC1.26
unnamed: D1.A, R5.1
unnamed: R2.2, SCL.2
unnamed: R3.2, SDA.2
unnamed: D4.K, DS1.1 (K1), R7.1
unnamed: D5.K, DS2.1 (K1), R9.1
unnamed: D10.K, DS4.1 (K1), R13.1
unnamed: D12.K, DS5.1 (K1), R15.1
unnamed: D8.K, DS3.1 (K1), R11.1
unnamed: IC1.1, R16.1, SW1.1
unnamed: IC1.2, K1.3
unnamed: IC1.3, K1.2
unnamed: C1.2, IC1.9, Q1.2
SCL: I2C.3, I2C/2.3, IC1.28, SCL.1
SDA: I2C.2, I2C/2.2, IC1.27, SDA.1

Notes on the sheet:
+5V DATA 0V
+5V SDA SCL 0V
PULL-UP
I2C BUS

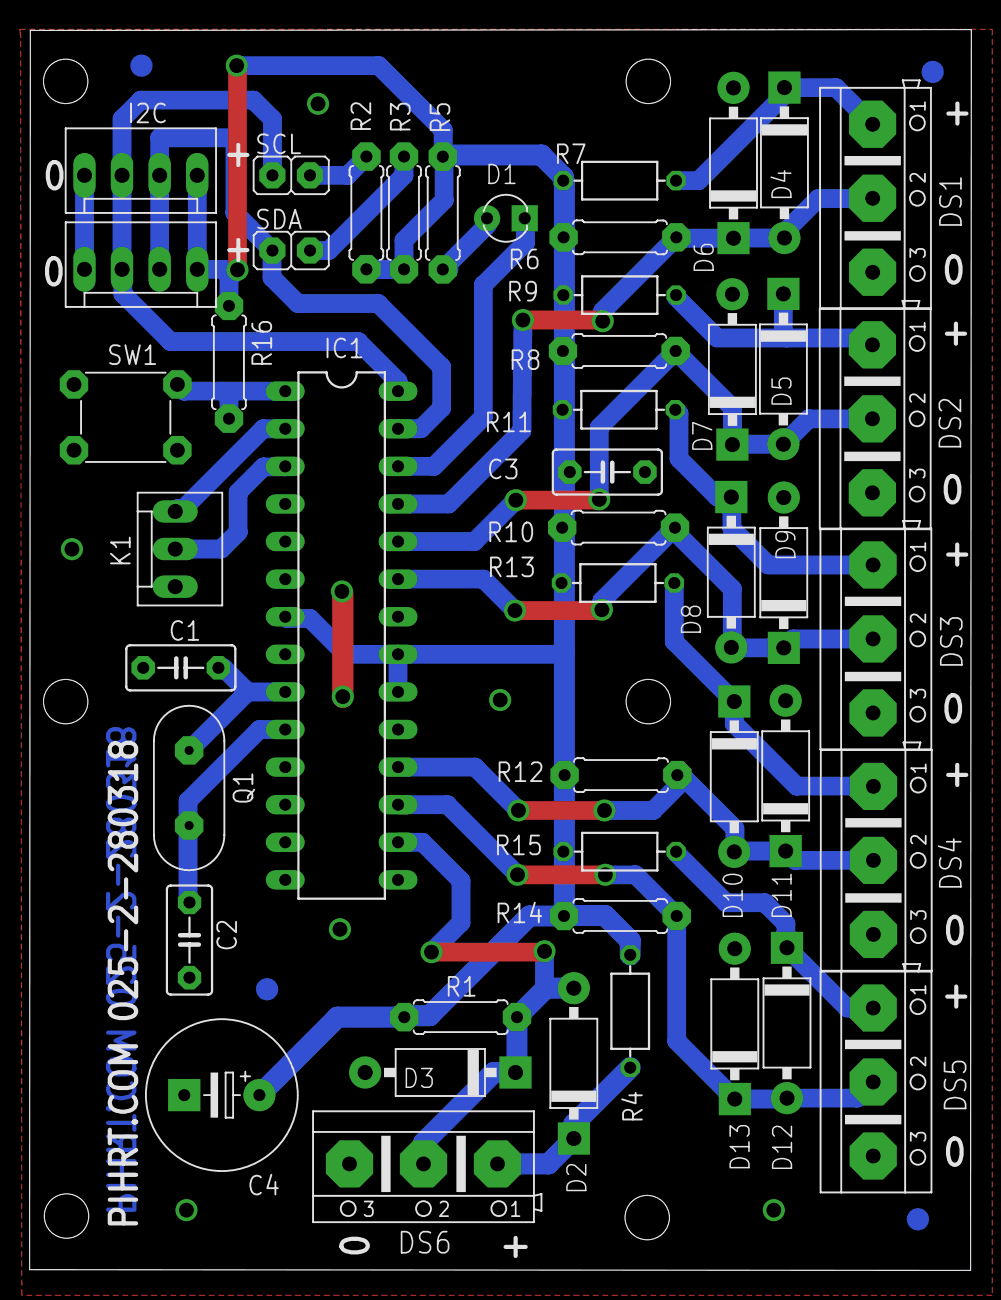
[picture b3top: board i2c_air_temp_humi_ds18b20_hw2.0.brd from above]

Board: 2 copper layers, 63.6 x 83.8 mm, 47 parts (0 on the bottom side), 25 nets.

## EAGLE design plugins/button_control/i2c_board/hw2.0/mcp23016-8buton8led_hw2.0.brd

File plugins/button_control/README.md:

Button Control Readme
====

Tested in Python 3+

This plugin uses a circuit board with MCP23017 controller connected to the OSPy Sprinkler board via the I2C interface.  
This plug-in includes eight buttons with optional functions and signalisating via eicht LEDs.  
Visit <a href="https://pihrt.com/clanky/moje-raspberry-pi-plugin-ospy-8-tlacitek-8-led">Martin Pihrt's blog</a> for more information.
I2C address for MCP23017: 0x20 to 0x27.  

The plug-in includes an OSPy `plugin.json` manifest, registers its polling
worker with the shared plug-in runtime, uses the common stop signal, and
implements `health()`. Diagnostics reports enablement, worker state, configured
I2C address, latest successful controller read, and the latest communication
error. I2C bus handles are closed after each operation.

Plugin setup
-----------
* Check Use Button:  
  If checked use button plugin is enabled.  

* Address for MCP23017 controller:
  Selector for I2C address in range 0x20 to 0x27.  

* First stop:  
  First stop everything running and then start the program.   
  If we want to start a new program and add it to the running ones, we will leave this option off.  

* Select:  
  Run-now program 1  
  Run-now program 2  
  Run-now program 3  
  Run-now program 4  
  Run-now program 5  
  Run-now program 6  
  Run-now program 7  
  Run-now program 8  
  Restart system (OS system)  
  Shutdown system (OS system)  
  Stop stations  
  Enable scheduler  
  Disable Scheduler  
* Status:  
  Status window from the plugin.

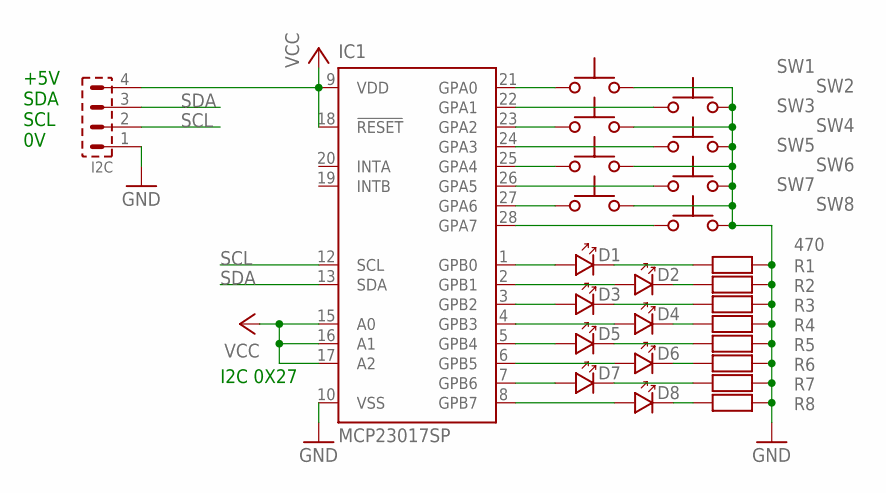
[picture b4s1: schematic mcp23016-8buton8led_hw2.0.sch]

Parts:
D1, D2, D3, D4, D5, D6, D7, D8: LED_5
I2C: S1G4_JUMP; S1G4_JUM
IC1: MCP23017SP; DIL28-3
R1: 470; R-5
R2, R3, R4, R5, R6, R7, R8: R_5; R-5
SW1, SW2, SW3, SW4, SW5, SW6, SW7, SW8: P-B1720

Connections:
GND: I2C.1, IC1.10 (VSS), R1.2, R2.2, R3.2, R4.2, R5.2, R6.2, R7.2, R8.2, SW1.2, SW2.2, SW3.2, SW4.2, SW5.2, SW6.2, SW7.2, SW8.2
unnamed: D1.A, IC1.1 (GPB0)
unnamed: D2.A, IC1.2 (GPB1)
unnamed: D3.A, IC1.3 (GPB2)
unnamed: D4.A, IC1.4 (GPB3)
unnamed: D5.A, IC1.5 (GPB4)
unnamed: D6.A, IC1.6 (GPB5)
unnamed: D7.A, IC1.7 (GPB6)
unnamed: D8.A, IC1.8 (GPB7)
unnamed: D1.K, R1.1
unnamed: D2.K, R2.1
unnamed: D3.K, R3.1
unnamed: D4.K, R4.1
unnamed: D5.K, R5.1
unnamed: D6.K, R6.1
unnamed: D7.K, R7.1
unnamed: D8.K, R8.1
unnamed: IC1.21 (GPA0), SW1.1
unnamed: IC1.22 (GPA1), SW2.1
unnamed: IC1.23 (GPA2), SW3.1
unnamed: IC1.24 (GPA3), SW4.1
unnamed: IC1.25 (GPA4), SW5.1
unnamed: IC1.26 (GPA5), SW6.1
unnamed: IC1.27 (GPA6), SW7.1
unnamed: IC1.28 (GPA7), SW8.1
SCL: I2C.2, IC1.12 (SCL)
SDA: I2C.3, IC1.13 (SDA)
VCC: I2C.4, IC1.9 (VDD), IC1.15 (A0), IC1.16 (A1), IC1.17 (A2), IC1.18 (!RESET)

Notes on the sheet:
I2C 0X27
+5V SDA SCL 0V

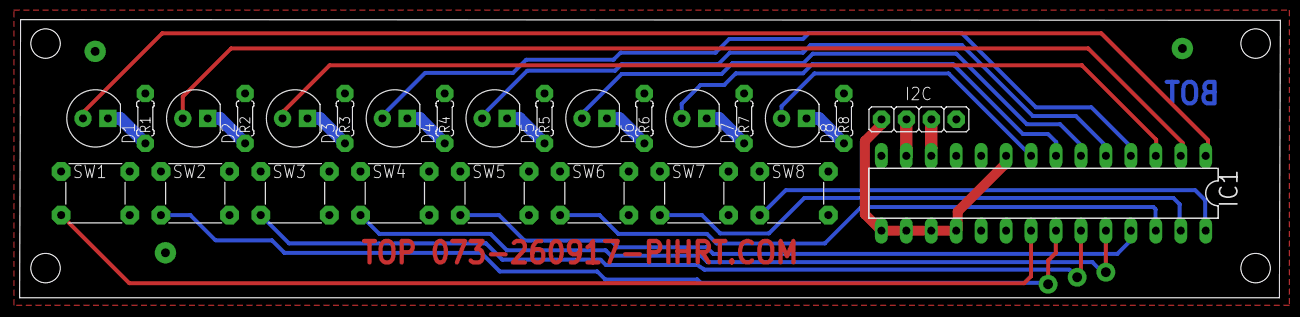
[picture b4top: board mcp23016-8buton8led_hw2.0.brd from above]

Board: 2 copper layers, 128.3 x 28.3 mm, 26 parts (0 on the bottom side), 28 nets.

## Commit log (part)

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2024-11-05 test
2024-11-06 completed (not sql tested)
2024-11-09 add email form
2024-11-09 i2c test btn
2024-11-11 fix find i2c
2024-11-13 not ready
2024-12-17 1PM Addon
2024-12-25 Add H&T sensor
2024-12-25 Add cloud error msg
2024-12-30 Add reading data over the local network
    not 100% tested
2025-01-01 Prepare for add to sensors search
2025-01-02 Add hw and gen
2025-01-03 fix to alsa
2025-01-27 Add tank monitor 4-20mA
2025-01-31 Add shelly sensors. LCD graphical display on web.
2025-01-31 Graphical switch on web
2025-01-31 if script_path not in pluginScripts
2025-02-03 Fix tank on homepage, add switch use script injection
2025-02-06 Add switch css and doc in help
2025-02-26 Fix string (Range for port is 80 to 65535)
2025-02-26 Add automation (not 100% tested)
2025-03-26 graph filtering
2025-03-29 Add filtering
2025-03-29 Add data options for sending
2025-03-31 Add shelly pro 3EM (not completed)
2025-04-03 Add revers power for PV (shelly pro 3EM)
2025-04-15 Add Wall Display
2025-04-15 not local for wall display
2025-04-15 Add PV Power and illuminance
2025-06-30 Fix: client has sent too many requests in a given amount of time
2025-07-01 fixed Removal of rain delay even if it should not have been removed. Just enter the settings page and delay was 0
2025-08-08 not ready is error
2025-10-28 Added Rollback
2025-10-29 Fixed js for translating string
2025-10-29 New plugin
2025-10-29 Auto refresh
2025-10-31 fix 303 See Other
2025-10-31 log to db and local json file
2025-10-31 Add graph
2025-11-02 Cosmetic fix
2026-06-26 Modernize air_temp_humi DS sensor selection and graph filtering
    - Add per-sensor DS18B20 enable flags for DS1-DS6
    - Keep existing DS/DHT public API compatible for other plugins
    - Hide disabled DS sensors from graph and log views
    - Preserve -127 as sensor error value and reset DS values on I2C read failure
    - Extend data_json with plugin/sensor enabled state and active DS indexes
    - Send air_temp_humi_plugin_update after settings changes
2026-06-26 Modernize ups_adj graph filtering and status display
    - Add AJAX-based graph filtering with quick ranges
    - Add Today, 24h, 7 days, 30 days, All, Reset, and no-data feedback
    - Allow graph_json to read dt_from and dt_to from query parameters
    - Replace old graph history form with compact filter controls
    - Add structured UPS state data for ups_json and data_json
    - Show live UPS state as colored OK/FAULT badge
2026-06-26 Unify graph filtering UI across monitor plugins
    - Apply AJAX-based graph filtering to all Flot graph plugins
    - Add common quick ranges: Today, 24h, 7 days, 30 days, All
    - Add manual From/To range controls, Reset, and no-data feedback
    - Remove old historyForm, Reload chart, Delete range, and Clear selection controls
    - Update graph_json endpoints to accept dt_from and dt_to query parameters
    - Keep legacy history settings in ping_monitor and speed_monitor for compatibility
2026-06-26 network_ping_monitor: add graph date range filters
    - add dt_from/dt_to options for graph filtering
    - filter local JSON and SQL graph records by selected date range
    - add quick graph ranges: Today, 24 h, 7 days, 30 days, All
    - keep existing record limit behavior
    - show an empty-state message when no records match the selected range
2026-06-26 HASS fix sensors
2026-06-26 Harden real_time and MQTT Home Assistant plugins
    - make real_time settings template safer for web.py AST compilation
    - add NTP socket timeout and bounded plugin stop join
    - avoid shell-based date commands in real_time
    - compare NTP time against current datetime correctly
    - handle stopped optional plugins in MQTT Home Assistant integration
2026-06-26 Harden plugin stop, network, shell, and dependency handling
    Harden plugin runtime behavior and hot reload safety
    - add bounded join timeouts to plugin stop handlers
    - add HTTP request timeouts to network-using plugins
    - reduce shell command usage where argument execution is sufficient
    - keep CLI Control shell execution but add timeout handling
    - guard air_temp_humi dependent plugins against stopped plugin state
2026-06-27 Improve system update version check responsiveness
    Run the System Update plugin version check asynchronously from the
    settings page so the web request no longer waits for slow GitHub/network
    operations. Add timeout handling for git status commands, show a
    "Checking..." state while refresh is running, and prevent duplicate
    manual refreshes from repeated clicks.
2026-06-27 Make system update status refresh asynchronous
    Add a JSON status endpoint for the System Update plugin and update the
    settings page to refresh status, logs, commit list, and action buttons in
    the background. The manual version check now starts via AJAX, shows a
    live "Checking..." state, and updates the page when the Git check
    finishes without requiring a browser refresh.
2026-06-27 Fix system update live status log rendering
    Clear the System Update plugin log before starting a manual asynchronous
    version check so repeated checks do not append duplicate status messages.
    Also render AJAX status log entries with real newline characters instead
    of displaying literal "\n" text in the status textarea.
2026-06-27 Fix mojibake in plugin unit strings
2026-06-27 Fix for i18n translate
2026-06-28 Add DS error filtering option to Home Assistant MQTT plugin
    - Add a new "Send errors" setting for DS1-DS6 publishing
    - Keep existing behavior by default by sending DS error values
    - Skip DS18B20 values below -100 when the setting is disabled
    - Add the setting to the plugin web form for i18n translation
2026-06-28 fix post
2026-06-28 Update Home Assistant MQTT plugin docs and DS error handling
    - Add "Send errors" option for DS1-DS6 temperature publishing
    - Keep existing behavior by default by sending DS error values
    - Suppress DS18B20 values below -100 when error sending is disabled
    - Make DS error filtering tolerant of numeric string values
    - Fix settings page notice handler argument count
    - Document available Home Assistant devices and entities in help page
2026-06-28 Guard MQTT client access in Home Assistant plugin
2026-06-28 Retry DS18B20 reads before reporting errors
2026-06-29 Improve DS18B20 I2C error handling in air temp plugin
2026-06-29 Add I2C guard and CSRF to real time plugin
2026-06-29 Add shared I2C locking and CSRF protection to I2C plugins
2026-06-29 Auto-refresh Shelly status and add CSRF protection
2026-06-29 Move shared I2C guard into OSPy core namespace
2026-06-29 Relax I2C guard timeout and handle busy button reads
2026-06-29 Fix wind counter None handling with shared I2C guard
2026-06-29 Colorize system debug log levels and add CSRF
2026-06-29 Add CSRF protection across plugins
2026-06-29 Fixed verify_csrf
2026-06-30 Complete plugin CSRF audit
2026-06-30 Reduce CHMI radar download attempts
2026-06-30 Update CHMI radar source and improve settings UI
    - Changed CHMI radar image download source from the old www.chmi.cz URL to the current CHMI open data endpoint.
    - Added validation that downloaded radar data is a real PNG image before processing it.
    - Reduced radar download fallback attempts to 3 older timestamps to avoid excessive requests to CHMI servers.
    - Added a User-Agent and request timeout for radar image downloads.
    - Documented the new CHMI open data radar endpoint in the plugin README.
    - Added a new "Send to HW map" option for enabling or disabling HTTP POST requests to the external hardware LED map.
2026-06-30 Add CHMI radar map animation from RAM cache
2026-06-30 Document CHMI radar animation timeline and forecast
2026-06-30 Improve CHMI rain delay detection area
2026-06-30 Add CHMI animated radar widget to home page
2026-06-30 Fix CHMI home widget responsive positioning
2026-06-30 Constrain CHMI home widget inside status panel
2026-06-30 Fix voice plugin sound templates
2026-06-30 Improve button control program selection

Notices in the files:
parts and their libraries:
Copyright (C) PaJa 2001-2014
Copyright (C) PaJa 2011-2014
